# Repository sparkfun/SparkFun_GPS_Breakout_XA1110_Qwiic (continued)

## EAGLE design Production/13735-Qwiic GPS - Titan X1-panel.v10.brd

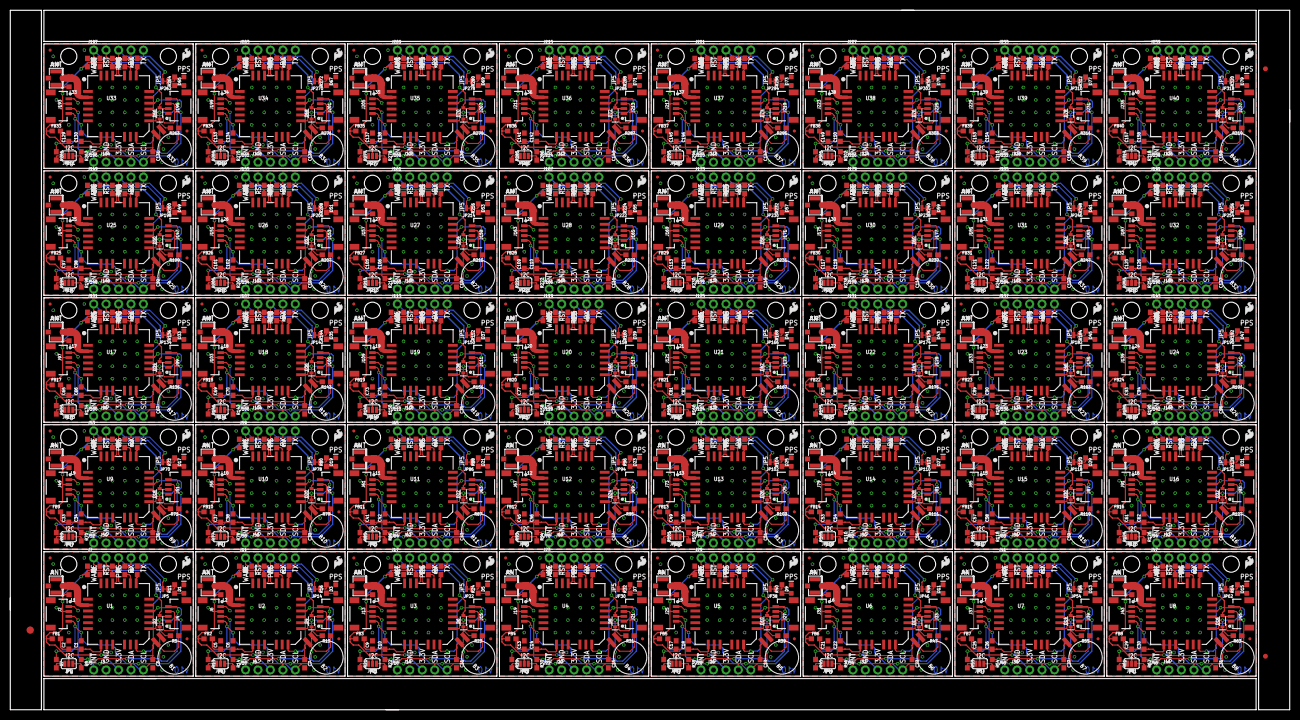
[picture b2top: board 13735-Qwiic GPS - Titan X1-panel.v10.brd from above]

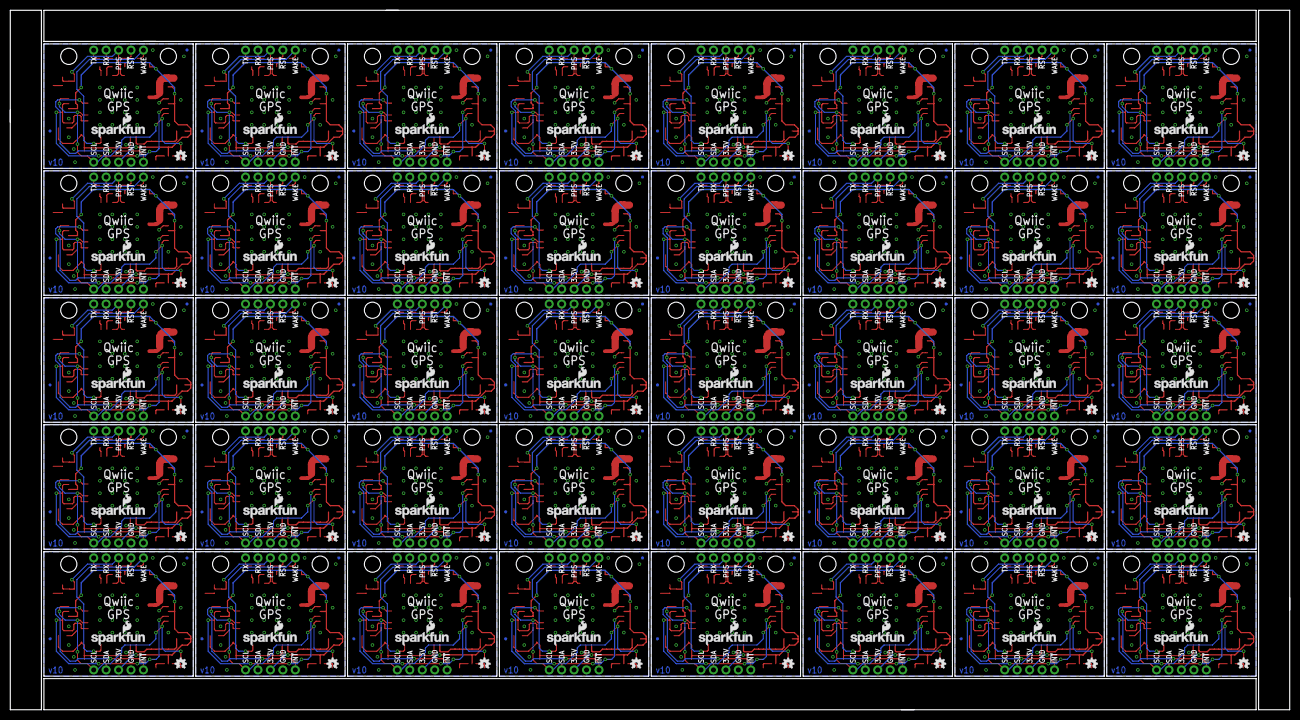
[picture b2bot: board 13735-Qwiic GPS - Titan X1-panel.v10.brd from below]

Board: 2 copper layers, 261.1 x 142.7 mm, 1403 parts (160 on the bottom side), 800 nets.

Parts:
B1, B2, B3, B4, B5, B6, B7, B8, B9, B10, B11, B12, B13, B14, B15, B16, B17, B18, B19, B20, B21, B22, B23, B24, B25, B26, B27, B28, B29, B30, B31, B32, B33, B34, B35, B36, B37, B38, B39, B40: 6.8MM_COIN_CELL; BATTCON-6.8MM
C1, C6, C10, C14, C18, C22, C26, C30, C34, C38, C42, C46, C50, C54, C58, C62, C66, C70, C74, C78, C82, C86, C90, C94, C98, C102, C106, C110, C114, C118, C122, C126, C130, C134, C138, C142, C146, C150, C154, C158: 0.1uF; 0603
C2, C3, C4, C5, C7, C8, C9, C11, C12, C13, C15, C16, C17, C19, C20, C21, C23, C24, C25, C27, C28, C29, C31, C32, C33, C35, C36, C37, C39, C40, C41, C43, C44, C45, C47, C48, C49, C51, C52, C53, C55, C56, C57, C59, C60, C61, C63, C64, C65, C67, C68, C69, C71, C72, C73, C75, C76, C77, C79, C80, C81, C83, C84, C85, C87, C88, C89, C91, C92, C93, C95, C96, C97, C99, C100, C101, C103, C104, C105, C107, C108, C109, C111, C112, C113, C115, C116, C117, C119, C120, C121, C123, C124, C125, C127, C128, C129, C131, C132, C133, C135, C136, C137, C139, C140, C141, C143, C144, C145, C147, C148, C149, C151, C152, C153, C155, C156, C157, C159, C160: 1.0uF; 0603
D1, D3, D5, D7, D9, D11, D13, D15, D17, D19, D21, D23, D25, D27, D29, D31, D33, D35, D37, D39, D41, D43, D45, D47, D49, D51, D53, D55, D57, D59, D61, D63, D65, D67, D69, D71, D73, D75, D77, D79: BLUE; LED-0603
D2, D4, D6, D8, D10, D12, D14, D16, D18, D20, D22, D24, D26, D28, D30, D32, D34, D36, D38, D40, D42, D44, D46, D48, D50, D52, D54, D56, D58, D60, D62, D64, D66, D68, D70, D72, D74, D76, D78, D80: 0.5A/40V/420mV; SOD-323
E$1: FIDUCIAL-1.5X3
E$7, E$8: FIDUCIAL-1X2
FB1, FB2, FB3, FB4, FB5, FB6, FB7, FB8, FB9, FB10, FB11, FB12, FB13, FB14, FB15, FB16, FB17, FB18, FB19, FB20, FB21, FB22, FB23, FB24, FB25, FB26, FB27, FB28, FB29, FB30, FB31, FB32, FB33, FB34, FB35, FB36, FB37, FB38, FB39, FB40: 600Ohm/100MHz; 0603
J1, J12, J18, J24, J30, J36, J42, J48, J54, J60, J66, J72, J78, J84, J90, J96, J102, J108, J114, J120, J126, J132, J138, J144, J150, J156, J162, J168, J174, J180, J186, J192, J198, J204, J210, J216, J222, J228, J234, J240: U.FL
J2, J4, J6, J9, J13, J15, J19, J21, J25, J27, J31, J33, J37, J39, J43, J45, J49, J51, J55, J57, J61, J63, J67, J69, J73, J75, J79, J81, J85, J87, J91, J93, J97, J99, J103, J105, J109, J111, J115, J117, J121, J123, J127, J129, J133, J135, J139, J141, J145, J147, J151, J153, J157, J159, J163, J165, J169, J171, J175, J177, J181, J183, J187, J189, J193, J195, J199, J201, J205, J207, J211, J213, J217, J219, J223, J225, J229, J231, J235, J237: Qwiic Right Angle; 1X04_1MM_RA
J3, J8, J14, J20, J26, J32, J38, J44, J50, J56, J62, J68, J74, J80, J86, J92, J98, J104, J110, J116, J122, J128, J134, J140, J146, J152, J158, J164, J170, J176, J182, J188, J194, J200, J206, J212, J218, J224, J230, J236: PTH; 1X04_NO_SILK
J5, J10, J16, J22, J28, J34, J40, J46, J52, J58, J64, J70, J76, J82, J88, J94, J100, J106, J112, J118, J124, J130, J136, J142, J148, J154, J160, J166, J172, J178, J184, J190, J196, J202, J208, J214, J220, J226, J232, J238: 1X01_NO_SILK
J7, J11, J17, J23, J29, J35, J41, J47, J53, J59, J65, J71, J77, J83, J89, J95, J101, J107, J113, J119, J125, J131, J137, J143, J149, J155, J161, J167, J173, J179, J185, J191, J197, J203, J209, J215, J221, J227, J233, J239: 1X05_NO_SILK
JP1, JP13, JP21, JP29, JP37, JP45, JP53, JP61, JP69, JP77, JP85, JP93, JP101, JP109, JP117, JP125, JP133, JP141, JP149, JP157, JP165, JP173, JP181, JP189, JP197, JP205, JP213, JP221, JP229, JP237, JP245, JP253, JP261, JP269, JP277, JP285, JP293, JP301, JP309, JP317: SMT-JUMPER_3_2-NC_PASTE_SILK
JP2, JP6, JP7, JP8, JP11, JP12, JP15, JP16, JP19, JP20, JP23, JP24, JP27, JP28, JP31, JP32, JP35, JP36, JP39, JP40, JP43, JP44, JP47, JP48, JP51, JP52, JP55, JP56, JP59, JP60, JP63, JP64, JP67, JP68, JP71, JP72, JP75, JP76, JP79, JP80, JP83, JP84, JP87, JP88, JP91, JP92, JP95, JP96, JP99, JP100, JP103, JP104, JP107, JP108, JP111, JP112, JP115, JP116, JP119, JP120, JP123, JP124, JP127, JP128, JP131, JP132, JP135, JP136, JP139, JP140, JP143, JP144, JP147, JP148, JP151, JP152, JP155, JP156, JP159, JP160, JP163, JP164, JP167, JP168, JP171, JP172, JP175, JP176, JP179, JP180, JP183, JP184, JP187, JP188, JP191, JP192, JP195, JP196, JP199, JP200, JP203, JP204, JP207, JP208, JP211, JP212, JP215, JP216, JP219, JP220, JP223, JP224, JP227, JP228, JP231, JP232, JP235, JP236, JP239, JP240, JP243, JP244, JP247, JP248, JP251, JP252, JP255, JP256, JP259, JP260, JP263, JP264, JP267, JP268, JP271, JP272, JP275, JP276, JP279, JP280, JP283, JP284, JP287, JP288, JP291, JP292, JP295, JP296, JP299, JP300, JP303, JP304, JP307, JP308, JP311, JP312, JP315, JP316, JP319, JP320: FIDUCIALUFIDUCIAL; MICRO-FIDUCIAL
JP3, JP4, JP9, JP10, JP17, JP18, JP25, JP26, JP33, JP34, JP41, JP42, JP49, JP50, JP57, JP58, JP65, JP66, JP73, JP74, JP81, JP82, JP89, JP90, JP97, JP98, JP105, JP106, JP113, JP114, JP121, JP122, JP129, JP130, JP137, JP138, JP145, JP146, JP153, JP154, JP161, JP162, JP169, JP170, JP177, JP178, JP185, JP186, JP193, JP194, JP201, JP202, JP209, JP210, JP217, JP218, JP225, JP226, JP233, JP234, JP241, JP242, JP249, JP250, JP257, JP258, JP265, JP266, JP273, JP274, JP281, JP282, JP289, JP290, JP297, JP298, JP305, JP306, JP313, JP314: STAND-OFF
JP5, JP14, JP22, JP30, JP38, JP46, JP54, JP62, JP70, JP78, JP86, JP94, JP102, JP110, JP118, JP126, JP134, JP142, JP150, JP158, JP166, JP174, JP182, JP190, JP198, JP206, JP214, JP222, JP230, JP238, JP246, JP254, JP262, JP270, JP278, JP286, JP294, JP302, JP310, JP318: SMT-JUMPER_2_NC_TRACE_NO-SILK
L1, L2, L3, L4, L5, L6, L7, L8, L9, L10, L11, L12, L13, L14, L15, L16, L17, L18, L19, L20, L21, L22, L23, L24, L25, L26, L27, L28, L29, L30, L31, L32, L33, L34, L35, L36, L37, L38, L39, L40: 33nH/±5%/500mA; 0603
LOGO1, LOGO3, LOGO5, LOGO7, LOGO9, LOGO11, LOGO13, LOGO15, LOGO17, LOGO19, LOGO21, LOGO23, LOGO25, LOGO27, LOGO29, LOGO31, LOGO33, LOGO35, LOGO37, LOGO39, LOGO41, LOGO43, LOGO45, LOGO47, LOGO49, LOGO51, LOGO53, LOGO55, LOGO57, LOGO59, LOGO61, LOGO63, LOGO65, LOGO67, LOGO69, LOGO71, LOGO73, LOGO75, LOGO77, LOGO79: OSHW-LOGOMINI; OSHW-LOGO-MINI
LOGO2, LOGO4, LOGO6, LOGO8, LOGO10, LOGO12, LOGO14, LOGO16, LOGO18, LOGO20, LOGO22, LOGO24, LOGO26, LOGO28, LOGO30, LOGO32, LOGO34, LOGO36, LOGO38, LOGO40, LOGO42, LOGO44, LOGO46, LOGO48, LOGO50, LOGO52, LOGO54, LOGO56, LOGO58, LOGO60, LOGO62, LOGO64, LOGO66, LOGO68, LOGO70, LOGO72, LOGO74, LOGO76, LOGO78, LOGO80: SFE_LOGO_NAME_FLAME.1_INCH; SFE_LOGO_NAME_FLAME_.1
R1, R2, R4, R9, R17, R18, R25, R26, R33, R34, R41, R42, R49, R50, R57, R58, R65, R66, R73, R74, R81, R82, R89, R90, R97, R98, R105, R106, R113, R114, R121, R122, R129, R130, R137, R138, R145, R146, R153, R154, R161, R162, R169, R170, R177, R178, R185, R186, R193, R194, R201, R202, R209, R210, R217, R218, R225, R226, R233, R234, R241, R242, R249, R250, R257, R258, R265, R266, R273, R274, R281, R282, R289, R290, R297, R298, R305, R306, R313, R314: 10k; 0603
R3, R6, R10, R11, R12, R16, R19, R20, R24, R27, R28, R32, R35, R36, R40, R43, R44, R48, R51, R52, R56, R59, R60, R64, R67, R68, R72, R75, R76, R80, R83, R84, R88, R91, R92, R96, R99, R100, R104, R107, R108, R112, R115, R116, R120, R123, R124, R128, R131, R132, R136, R139, R140, R144, R147, R148, R152, R155, R156, R160, R163, R164, R168, R171, R172, R176, R179, R180, R184, R187, R188, R192, R195, R196, R200, R203, R204, R208, R211, R212, R216, R219, R220, R224, R227, R228, R232, R235, R236, R240, R243, R244, R248, R251, R252, R256, R259, R260, R264, R267, R268, R272, R275, R276, R280, R283, R284, R288, R291, R292, R296, R299, R300, R304, R307, R308, R312, R315, R316, R320: 470; 0603
R5, R15, R23, R31, R39, R47, R55, R63, R71, R79, R87, R95, R103, R111, R119, R127, R135, R143, R151, R159, R167, R175, R183, R191, R199, R207, R215, R223, R231, R239, R247, R255, R263, R271, R279, R287, R295, R303, R311, R319: 1k; 0603
R7, R8, R13, R14, R21, R22, R29, R30, R37, R38, R45, R46, R53, R54, R61, R62, R69, R70, R77, R78, R85, R86, R93, R94, R101, R102, R109, R110, R117, R118, R125, R126, R133, R134, R141, R142, R149, R150, R157, R158, R165, R166, R173, R174, R181, R182, R189, R190, R197, R198, R205, R206, R213, R214, R221, R222, R229, R230, R237, R238, R245, R246, R253, R254, R261, R262, R269, R270, R277, R278, R285, R286, R293, R294, R301, R302, R309, R310, R317, R318: 4.7k; 0603
U1, U2, U3, U4, U5, U6, U7, U8, U9, U10, U11, U12, U13, U14, U15, U16, U17, U18, U19, U20, U21, U22, U23, U24, U25, U26, U27, U28, U29, U30, U31, U32, U33, U34, U35, U36, U37, U38, U39, U40: Titan X1 GPS; TITAN_X1_GPS
U$1, U$2, U$3, U$4, U$5, U$6, U$7, U$8, U$9, U$10, U$11, U$12, U$13, U$14, U$15, U$16, U$17, U$18, U$19, U$20, U$21, U$22, U$23, U$24, U$25, U$26, U$27, U$28, U$29, U$30, U$31, U$32, U$33, U$34, U$35, U$36, U$37, U$38, U$39, U$40: SFE_LOGO_FLAME_.1

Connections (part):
3.3V: C4.2, D2.A, FB1.1, J2.2, J3.2, J4.2, JP1.2, L1.2, R2.2
3.3V1: C8.2, D4.A, FB2.1, J6.2, J8.2, J9.2, JP13.2, L2.2, R9.2
3.3V2: C12.2, D6.A, FB3.1, J13.2, J14.2, J15.2, JP21.2, L3.2, R18.2
3.3V3: C16.2, D8.A, FB4.1, J19.2, J20.2, J21.2, JP29.2, L4.2, R26.2
3.3V4: C20.2, D10.A, FB5.1, J25.2, J26.2, J27.2, JP37.2, L5.2, R34.2
3.3V5: C24.2, D12.A, FB6.1, J31.2, J32.2, J33.2, JP45.2, L6.2, R42.2
3.3V6: C28.2, D14.A, FB7.1, J37.2, J38.2, J39.2, JP53.2, L7.2, R50.2
3.3V7: C32.2, D16.A, FB8.1, J43.2, J44.2, J45.2, JP61.2, L8.2, R58.2
3.3V8: C36.2, D18.A, FB9.1, J49.2, J50.2, J51.2, JP69.2, L9.2, R66.2
3.3V9: C40.2, D20.A, FB10.1, J55.2, J56.2, J57.2, JP77.2, L10.2, R74.2
3.3V10: C44.2, D22.A, FB11.1, J61.2, J62.2, J63.2, JP85.2, L11.2, R82.2
3.3V11: C48.2, D24.A, FB12.1, J67.2, J68.2, J69.2, JP93.2, L12.2, R90.2
3.3V12: C52.2, D26.A, FB13.1, J73.2, J74.2, J75.2, JP101.2, L13.2, R98.2
3.3V13: C56.2, D28.A, FB14.1, J79.2, J80.2, J81.2, JP109.2, L14.2, R106.2
3.3V14: C60.2, D30.A, FB15.1, J85.2, J86.2, J87.2, JP117.2, L15.2, R114.2
3.3V15: C64.2, D32.A, FB16.1, J91.2, J92.2, J93.2, JP125.2, L16.2, R122.2
3.3V16: C68.2, D34.A, FB17.1, J97.2, J98.2, J99.2, JP133.2, L17.2, R130.2
3.3V17: C72.2, D36.A, FB18.1, J103.2, J104.2, J105.2, JP141.2, L18.2, R138.2
3.3V18: C76.2, D38.A, FB19.1, J109.2, J110.2, J111.2, JP149.2, L19.2, R146.2
3.3V19: C80.2, D40.A, FB20.1, J115.2, J116.2, J117.2, JP157.2, L20.2, R154.2
3.3V20: C84.2, D42.A, FB21.1, J121.2, J122.2, J123.2, JP165.2, L21.2, R162.2
3.3V21: C88.2, D44.A, FB22.1, J127.2, J128.2, J129.2, JP173.2, L22.2, R170.2
3.3V22: C92.2, D46.A, FB23.1, J133.2, J134.2, J135.2, JP181.2, L23.2, R178.2
3.3V23: C96.2, D48.A, FB24.1, J139.2, J140.2, J141.2, JP189.2, L24.2, R186.2
3.3V24: C100.2, D50.A, FB25.1, J145.2, J146.2, J147.2, JP197.2, L25.2, R194.2
3.3V25: C104.2, D52.A, FB26.1, J151.2, J152.2, J153.2, JP205.2, L26.2, R202.2
3.3V26: C108.2, D54.A, FB27.1, J157.2, J158.2, J159.2, JP213.2, L27.2, R210.2
3.3V27: C112.2, D56.A, FB28.1, J163.2, J164.2, J165.2, JP221.2, L28.2, R218.2
3.3V28: C116.2, D58.A, FB29.1, J169.2, J170.2, J171.2, JP229.2, L29.2, R226.2
3.3V29: C120.2, D60.A, FB30.1, J175.2, J176.2, J177.2, JP237.2, L30.2, R234.2
3.3V30: C124.2, D62.A, FB31.1, J181.2, J182.2, J183.2, JP245.2, L31.2, R242.2
3.3V31: C128.2, D64.A, FB32.1, J187.2, J188.2, J189.2, JP253.2, L32.2, R250.2
3.3V32: C132.2, D66.A, FB33.1, J193.2, J194.2, J195.2, JP261.2, L33.2, R258.2
3.3V33: C136.2, D68.A, FB34.1, J199.2, J200.2, J201.2, JP269.2, L34.2, R266.2
3.3V34: C140.2, D70.A, FB35.1, J205.2, J206.2, J207.2, JP277.2, L35.2, R274.2
3.3V35: C144.2, D72.A, FB36.1, J211.2, J212.2, J213.2, JP285.2, L36.2, R282.2
3.3V36: C148.2, D74.A, FB37.1, J217.2, J218.2, J219.2, JP293.2, L37.2, R290.2
3.3V37: C152.2, D76.A, FB38.1, J223.2, J224.2, J225.2, JP301.2, L38.2, R298.2
3.3V38: C156.2, D78.A, FB39.1, J229.2, J230.2, J231.2, JP309.2, L39.2, R306.2
3.3V39: C160.2, D80.A, FB40.1, J235.2, J236.2, J237.2, JP317.2, L40.2, R314.2
!RESET: J7.2, R2.1, U1.22
!RESET1: J11.2, R9.1, U2.22
!RESET2: J17.2, R18.1, U3.22
!RESET3: J23.2, R26.1, U4.22
!RESET4: J29.2, R34.1, U5.22
!RESET5: J35.2, R42.1, U6.22
!RESET6: J41.2, R50.1, U7.22
!RESET7: J47.2, R58.1, U8.22
!RESET8: J53.2, R66.1, U9.22
!RESET9: J59.2, R74.1, U10.22
!RESET10: J65.2, R82.1, U11.22
!RESET11: J71.2, R90.1, U12.22
!RESET12: J77.2, R98.1, U13.22
!RESET13: J83.2, R106.1, U14.22
!RESET14: J89.2, R114.1, U15.22
!RESET15: J95.2, R122.1, U16.22
!RESET16: J101.2, R130.1, U17.22
!RESET17: J107.2, R138.1, U18.22
!RESET18: J113.2, R146.1, U19.22
!RESET19: J119.2, R154.1, U20.22
!RESET20: J125.2, R162.1, U21.22
!RESET21: J131.2, R170.1, U22.22
!RESET22: J137.2, R178.1, U23.22
!RESET23: J143.2, R186.1, U24.22
!RESET24: J149.2, R194.1, U25.22
!RESET25: J155.2, R202.1, U26.22
!RESET26: J161.2, R210.1, U27.22
!RESET27: J167.2, R218.1, U28.22
!RESET28: J173.2, R226.1, U29.22
!RESET29: J179.2, R234.1, U30.22
!RESET30: J185.2, R242.1, U31.22
!RESET31: J191.2, R250.1, U32.22
!RESET32: J197.2, R258.1, U33.22
!RESET33: J203.2, R266.1, U34.22
!RESET34: J209.2, R274.1, U35.22
!RESET35: J215.2, R282.1, U36.22
!RESET36: J221.2, R290.1, U37.22
!RESET37: J227.2, R298.1, U38.22
!RESET38: J233.2, R306.1, U39.22
!RESET39: J239.2, R314.1, U40.22
BACKUP: B1.+, C3.1, R5.1, U1.8
BACKUP1: B2.+, C7.1, R15.1, U2.8
BACKUP2: B3.+, C11.1, R23.1, U3.8
BACKUP3: B4.+, C15.1, R31.1, U4.8
BACKUP4: B5.+, C19.1, R39.1, U5.8
BACKUP5: B6.+, C23.1, R47.1, U6.8
BACKUP6: B7.+, C27.1, R55.1, U7.8
BACKUP7: B8.+, C31.1, R63.1, U8.8
BACKUP8: B9.+, C35.1, R71.1, U9.8
BACKUP9: B10.+, C39.1, R79.1, U10.8
BACKUP10: B11.+, C43.1, R87.1, U11.8
BACKUP11: B12.+, C47.1, R95.1, U12.8
BACKUP12: B13.+, C51.1, R103.1, U13.8
BACKUP13: B14.+, C55.1, R111.1, U14.8
BACKUP14: B15.+, C59.1, R119.1, U15.8
BACKUP15: B16.+, C63.1, R127.1, U16.8
BACKUP16: B17.+, C67.1, R135.1, U17.8
BACKUP17: B18.+, C71.1, R143.1, U18.8
BACKUP18: B19.+, C75.1, R151.1, U19.8
BACKUP19: B20.+, C79.1, R159.1, U20.8
BACKUP20: B21.+, C83.1, R167.1, U21.8
BACKUP21: B22.+, C87.1, R175.1, U22.8
BACKUP22: B23.+, C91.1, R183.1, U23.8
BACKUP23: B24.+, C95.1, R191.1, U24.8
BACKUP24: B25.+, C99.1, R199.1, U25.8
BACKUP25: B26.+, C103.1, R207.1, U26.8
BACKUP26: B27.+, C107.1, R215.1, U27.8
BACKUP27: B28.+, C111.1, R223.1, U28.8
BACKUP28: B29.+, C115.1, R231.1, U29.8
BACKUP29: B30.+, C119.1, R239.1, U30.8
BACKUP30: B31.+, C123.1, R247.1, U31.8
BACKUP31: B32.+, C127.1, R255.1, U32.8
BACKUP32: B33.+, C131.1, R263.1, U33.8
BACKUP33: B34.+, C135.1, R271.1, U34.8
BACKUP34: B35.+, C139.1, R279.1, U35.8
BACKUP35: B36.+, C143.1, R287.1, U36.8
BACKUP36: B37.+, C147.1, R295.1, U37.8
BACKUP37: B38.+, C151.1, R303.1, U38.8
BACKUP38: B39.+, C155.1, R311.1, U39.8
BACKUP39: B40.+, C159.1, R319.1, U40.8
EXT_ANT: J1.FEED, L1.1, U1.2
EXT_ANT1: J12.FEED, L2.1, U2.2
EXT_ANT2: J18.FEED, L3.1, U3.2
EXT_ANT3: J24.FEED, L4.1, U4.2
EXT_ANT4: J30.FEED, L5.1, U5.2
EXT_ANT5: J36.FEED, L6.1, U6.2
EXT_ANT6: J42.FEED, L7.1, U7.2
EXT_ANT7: J48.FEED, L8.1, U8.2
EXT_ANT8: J54.FEED, L9.1, U9.2
EXT_ANT9: J60.FEED, L10.1, U10.2
EXT_ANT10: J66.FEED, L11.1, U11.2
EXT_ANT11: J72.FEED, L12.1, U12.2
EXT_ANT12: J78.FEED, L13.1, U13.2
EXT_ANT13: J84.FEED, L14.1, U14.2
EXT_ANT14: J90.FEED, L15.1, U15.2
EXT_ANT15: J96.FEED, L16.1, U16.2
EXT_ANT16: J102.FEED, L17.1, U17.2
EXT_ANT17: J108.FEED, L18.1, U18.2
EXT_ANT18: J114.FEED, L19.1, U19.2
EXT_ANT19: J120.FEED, L20.1, U20.2
EXT_ANT20: J126.FEED, L21.1, U21.2
EXT_ANT21: J132.FEED, L22.1, U22.2
EXT_ANT22: J138.FEED, L23.1, U23.2
EXT_ANT23: J144.FEED, L24.1, U24.2
EXT_ANT24: J150.FEED, L25.1, U25.2
EXT_ANT25: J156.FEED, L26.1, U26.2
EXT_ANT26: J162.FEED, L27.1, U27.2
EXT_ANT27: J168.FEED, L28.1, U28.2
EXT_ANT28: J174.FEED, L29.1, U29.2
EXT_ANT29: J180.FEED, L30.1, U30.2
EXT_ANT30: J186.FEED, L31.1, U31.2
EXT_ANT31: J192.FEED, L32.1, U32.2
EXT_ANT32: J198.FEED, L33.1, U33.2
EXT_ANT33: J204.FEED, L34.1, U34.2
EXT_ANT34: J210.FEED, L35.1, U35.2
EXT_ANT35: J216.FEED, L36.1, U36.2
EXT_ANT36: J222.FEED, L37.1, U37.2
EXT_ANT37: J228.FEED, L38.1, U38.2
EXT_ANT38: J234.FEED, L39.1, U39.2
EXT_ANT39: J240.FEED, L40.1, U40.2
GND: B1.-, C1.2, C2.2, C3.2, C4.1, D1.C, J1.1, J1.2, J2.1, J3.1, J4.1, R1.1, U1.1, U1.3, U1.4, U1.5, U1.6, U1.9, U1.10, U1.11, U1.24
GND1: B2.-, C5.2, C6.2, C7.2, C8.1, D3.C, J6.1, J8.1, J9.1, J12.1, J12.2, R4.1, U2.1, U2.3, U2.4, U2.5, U2.6, U2.9, U2.10, U2.11, U2.24
GND2: B3.-, C9.2, C10.2, C11.2, C12.1, D5.C, J13.1, J14.1, J15.1, J18.1, J18.2, R17.1, U3.1, U3.3, U3.4, U3.5, U3.6, U3.9, U3.10, U3.11, U3.24
GND3: B4.-, C13.2, C14.2, C15.2, C16.1, D7.C, J19.1, J20.1, J21.1, J24.1, J24.2, R25.1, U4.1, U4.3, U4.4, U4.5, U4.6, U4.9, U4.10, U4.11, U4.24
GND4: B5.-, C17.2, C18.2, C19.2, C20.1, D9.C, J25.1, J26.1, J27.1, J30.1, J30.2, R33.1, U5.1, U5.3, U5.4, U5.5, U5.6, U5.9, U5.10, U5.11, U5.24
GND5: B6.-, C21.2, C22.2, C23.2, C24.1, D11.C, J31.1, J32.1, J33.1, J36.1, J36.2, R41.1, U6.1, U6.3, U6.4, U6.5, U6.6, U6.9, U6.10, U6.11, U6.24
GND6: B7.-, C25.2, C26.2, C27.2, C28.1, D13.C, J37.1, J38.1, J39.1, J42.1, J42.2, R49.1, U7.1, U7.3, U7.4, U7.5, U7.6, U7.9, U7.10, U7.11, U7.24
GND7: B8.-, C29.2, C30.2, C31.2, C32.1, D15.C, J43.1, J44.1, J45.1, J48.1, J48.2, R57.1, U8.1, U8.3, U8.4, U8.5, U8.6, U8.9, U8.10, U8.11, U8.24
GND8: B9.-, C33.2, C34.2, C35.2, C36.1, D17.C, J49.1, J50.1, J51.1, J54.1, J54.2, R65.1, U9.1, U9.3, U9.4, U9.5, U9.6, U9.9, U9.10, U9.11, U9.24
GND9: B10.-, C37.2, C38.2, C39.2, C40.1, D19.C, J55.1, J56.1, J57.1, J60.1, J60.2, R73.1, U10.1, U10.3, U10.4, U10.5, U10.6, U10.9, U10.10, U10.11, U10.24
GND10: B11.-, C41.2, C42.2, C43.2, C44.1, D21.C, J61.1, J62.1, J63.1, J66.1, J66.2, R81.1, U11.1, U11.3, U11.4, U11.5, U11.6, U11.9, U11.10, U11.11, U11.24
GND11: B12.-, C45.2, C46.2, C47.2, C48.1, D23.C, J67.1, J68.1, J69.1, J72.1, J72.2, R89.1, U12.1, U12.3, U12.4, U12.5, U12.6, U12.9, U12.10, U12.11, U12.24
GND12: B13.-, C49.2, C50.2, C51.2, C52.1, D25.C, J73.1, J74.1, J75.1, J78.1, J78.2, R97.1, U13.1, U13.3, U13.4, U13.5, U13.6, U13.9, U13.10, U13.11, U13.24
GND13: B14.-, C53.2, C54.2, C55.2, C56.1, D27.C, J79.1, J80.1, J81.1, J84.1, J84.2, R105.1, U14.1, U14.3, U14.4, U14.5, U14.6, U14.9, U14.10, U14.11, U14.24
GND14: B15.-, C57.2, C58.2, C59.2, C60.1, D29.C, J85.1, J86.1, J87.1, J90.1, J90.2, R113.1, U15.1, U15.3, U15.4, U15.5, U15.6, U15.9, U15.10, U15.11, U15.24
GND15: B16.-, C61.2, C62.2, C63.2, C64.1, D31.C, J91.1, J92.1, J93.1, J96.1, J96.2, R121.1, U16.1, U16.3, U16.4, U16.5, U16.6, U16.9, U16.10, U16.11, U16.24
GND16: B17.-, C65.2, C66.2, C67.2, C68.1, D33.C, J97.1, J98.1, J99.1, J102.1, J102.2, R129.1, U17.1, U17.3, U17.4, U17.5, U17.6, U17.9, U17.10, U17.11, U17.24
GND17: B18.-, C69.2, C70.2, C71.2, C72.1, D35.C, J103.1, J104.1, J105.1, J108.1, J108.2, R137.1, U18.1, U18.3, U18.4, U18.5, U18.6, U18.9, U18.10, U18.11, U18.24
GND18: B19.-, C73.2, C74.2, C75.2, C76.1, D37.C, J109.1, J110.1, J111.1, J114.1, J114.2, R145.1, U19.1, U19.3, U19.4, U19.5, U19.6, U19.9, U19.10, U19.11, U19.24
GND19: B20.-, C77.2, C78.2, C79.2, C80.1, D39.C, J115.1, J116.1, J117.1, J120.1, J120.2, R153.1, U20.1, U20.3, U20.4, U20.5, U20.6, U20.9, U20.10, U20.11, U20.24
GND20: B21.-, C81.2, C82.2, C83.2, C84.1, D41.C, J121.1, J122.1, J123.1, J126.1, J126.2, R161.1, U21.1, U21.3, U21.4, U21.5, U21.6, U21.9, U21.10, U21.11, U21.24
GND21: B22.-, C85.2, C86.2, C87.2, C88.1, D43.C, J127.1, J128.1, J129.1, J132.1, J132.2, R169.1, U22.1, U22.3, U22.4, U22.5, U22.6, U22.9, U22.10, U22.11, U22.24
GND22: B23.-, C89.2, C90.2, C91.2, C92.1, D45.C, J133.1, J134.1, J135.1, J138.1, J138.2, R177.1, U23.1, U23.3, U23.4, U23.5, U23.6, U23.9, U23.10, U23.11, U23.24
GND23: B24.-, C93.2, C94.2, C95.2, C96.1, D47.C, J139.1, J140.1, J141.1, J144.1, J144.2, R185.1, U24.1, U24.3, U24.4, U24.5, U24.6, U24.9, U24.10, U24.11, U24.24
GND24: B25.-, C97.2, C98.2, C99.2, C100.1, D49.C, J145.1, J146.1, J147.1, J150.1, J150.2, R193.1, U25.1, U25.3, U25.4, U25.5, U25.6, U25.9, U25.10, U25.11, U25.24
GND25: B26.-, C101.2, C102.2, C103.2, C104.1, D51.C, J151.1, J152.1, J153.1, J156.1, J156.2, R201.1, U26.1, U26.3, U26.4, U26.5, U26.6, U26.9, U26.10, U26.11, U26.24
GND26: B27.-, C105.2, C106.2, C107.2, C108.1, D53.C, J157.1, J158.1, J159.1, J162.1, J162.2, R209.1, U27.1, U27.3, U27.4, U27.5, U27.6, U27.9, U27.10, U27.11, U27.24
GND27: B28.-, C109.2, C110.2, C111.2, C112.1, D55.C, J163.1, J164.1, J165.1, J168.1, J168.2, R217.1, U28.1, U28.3, U28.4, U28.5, U28.6, U28.9, U28.10, U28.11, U28.24
GND28: B29.-, C113.2, C114.2, C115.2, C116.1, D57.C, J169.1, J170.1, J171.1, J174.1, J174.2, R225.1, U29.1, U29.3, U29.4, U29.5, U29.6, U29.9, U29.10, U29.11, U29.24
GND29: B30.-, C117.2, C118.2, C119.2, C120.1, D59.C, J175.1, J176.1, J177.1, J180.1, J180.2, R233.1, U30.1, U30.3, U30.4, U30.5, U30.6, U30.9, U30.10, U30.11, U30.24
GND30: B31.-, C121.2, C122.2, C123.2, C124.1, D61.C, J181.1, J182.1, J183.1, J186.1, J186.2, R241.1, U31.1, U31.3, U31.4, U31.5, U31.6, U31.9, U31.10, U31.11, U31.24
GND31: B32.-, C125.2, C126.2, C127.2, C128.1, D63.C, J187.1, J188.1, J189.1, J192.1, J192.2, R249.1, U32.1, U32.3, U32.4, U32.5, U32.6, U32.9, U32.10, U32.11, U32.24
GND32: B33.-, C129.2, C130.2, C131.2, C132.1, D65.C, J193.1, J194.1, J195.1, J198.1, J198.2, R257.1, U33.1, U33.3, U33.4, U33.5, U33.6, U33.9, U33.10, U33.11, U33.24
GND33: B34.-, C133.2, C134.2, C135.2, C136.1, D67.C, J199.1, J200.1, J201.1, J204.1, J204.2, R265.1, U34.1, U34.3, U34.4, U34.5, U34.6, U34.9, U34.10, U34.11, U34.24
GND34: B35.-, C137.2, C138.2, C139.2, C140.1, D69.C, J205.1, J206.1, J207.1, J210.1, J210.2, R273.1, U35.1, U35.3, U35.4, U35.5, U35.6, U35.9, U35.10, U35.11, U35.24
GND35: B36.-, C141.2, C142.2, C143.2, C144.1, D71.C, J211.1, J212.1, J213.1, J216.1, J216.2, R281.1, U36.1, U36.3, U36.4, U36.5, U36.6, U36.9, U36.10, U36.11, U36.24
GND36: B37.-, C145.2, C146.2, C147.2, C148.1, D73.C, J217.1, J218.1, J219.1, J222.1, J222.2, R289.1, U37.1, U37.3, U37.4, U37.5, U37.6, U37.9, U37.10, U37.11, U37.24
GND37: B38.-, C149.2, C150.2, C151.2, C152.1, D75.C, J223.1, J224.1, J225.1, J228.1, J228.2, R297.1, U38.1, U38.3, U38.4, U38.5, U38.6, U38.9, U38.10, U38.11, U38.24
GND38: B39.-, C153.2, C154.2, C155.2, C156.1, D77.C, J229.1, J230.1, J231.1, J234.1, J234.2, R305.1, U39.1, U39.3, U39.4, U39.5, U39.6, U39.9, U39.10, U39.11, U39.24
GND39: B40.-, C157.2, C158.2, C159.2, C160.1, D79.C, J235.1, J236.1, J237.1, J240.1, J240.2, R313.1, U40.1, U40.3, U40.4, U40.5, U40.6, U40.9, U40.10, U40.11, U40.24
INT: J5.1, U1.16
INT1: J10.1, U2.16
INT2: J16.1, U3.16
INT3: J22.1, U4.16
INT4: J28.1, U5.16
INT5: J34.1, U6.16
INT6: J40.1, U7.16
INT7: J46.1, U8.16
INT8: J52.1, U9.16
INT9: J58.1, U10.16
INT10: J64.1, U11.16
INT11: J70.1, U12.16
INT12: J76.1, U13.16
INT13: J82.1, U14.16
INT14: J88.1, U15.16
INT15: J94.1, U16.16
INT16: J100.1, U17.16
INT17: J106.1, U18.16
INT18: J112.1, U19.16
INT19: J118.1, U20.16
INT20: J124.1, U21.16
INT21: J130.1, U22.16
INT22: J136.1, U23.16
INT23: J142.1, U24.16
INT24: J148.1, U25.16
INT25: J154.1, U26.16
INT26: J160.1, U27.16
INT27: J166.1, U28.16
INT28: J172.1, U29.16
INT29: J178.1, U30.16
INT30: J184.1, U31.16
INT31: J190.1, U32.16
INT32: J196.1, U33.16
INT33: J202.1, U34.16
INT34: J208.1, U35.16
INT35: J214.1, U36.16
INT36: J220.1, U37.16
INT37: J226.1, U38.16
INT38: J232.1, U39.16
INT39: J238.1, U40.16
unnamed: JP13.1, R14.2
unnamed: D1.A, R11.1
unnamed: JP13.3, R13.2
unnamed: JP5.1, R11.2
unnamed: JP1.1, R8.2
unnamed: D2.C, R5.2
unnamed: D3.A, R16.1
unnamed: JP1.3, R7.2
unnamed: JP14.1, R16.2
unnamed: D4.C, R15.2
unnamed: JP21.1, R22.2
unnamed: JP21.3, R21.2
unnamed: D5.A, R24.1
unnamed: JP22.1, R24.2
unnamed: D6.C, R23.2
unnamed: JP29.1, R30.2
unnamed: JP29.3, R29.2
unnamed: D7.A, R32.1
unnamed: JP30.1, R32.2
unnamed: D8.C, R31.2
unnamed: JP37.1, R38.2
unnamed: JP37.3, R37.2
unnamed: D9.A, R40.1
unnamed: JP38.1, R40.2
unnamed: D10.C, R39.2
unnamed: JP45.1, R46.2
unnamed: JP45.3, R45.2
unnamed: D11.A, R48.1
unnamed: JP46.1, R48.2
unnamed: D12.C, R47.2
unnamed: JP53.1, R54.2
unnamed: JP53.3, R53.2
unnamed: D13.A, R56.1
unnamed: JP54.1, R56.2
unnamed: D14.C, R55.2
unnamed: JP61.1, R62.2
unnamed: JP61.3, R61.2
unnamed: D15.A, R64.1
unnamed: JP62.1, R64.2
unnamed: D16.C, R63.2
unnamed: JP69.1, R70.2
unnamed: JP69.3, R69.2
unnamed: D17.A, R72.1
unnamed: JP70.1, R72.2
unnamed: D18.C, R71.2
unnamed: JP77.1, R78.2
unnamed: JP77.3, R77.2
unnamed: D19.A, R80.1
unnamed: JP78.1, R80.2
unnamed: D20.C, R79.2
unnamed: JP85.1, R86.2
unnamed: JP85.3, R85.2
unnamed: D21.A, R88.1
unnamed: JP86.1, R88.2
unnamed: D22.C, R87.2
unnamed: JP93.1, R94.2
unnamed: JP93.3, R93.2
unnamed: D23.A, R96.1
unnamed: JP94.1, R96.2
unnamed: D24.C, R95.2
unnamed: JP101.1, R102.2
unnamed: JP101.3, R101.2
unnamed: D25.A, R104.1
unnamed: JP102.1, R104.2
unnamed: D26.C, R103.2
unnamed: JP109.1, R110.2
unnamed: JP109.3, R109.2
unnamed: D27.A, R112.1
unnamed: JP110.1, R112.2
unnamed: D28.C, R111.2
unnamed: JP117.1, R118.2
unnamed: JP117.3, R117.2
unnamed: D29.A, R120.1
unnamed: JP118.1, R120.2
unnamed: D30.C, R119.2
unnamed: JP125.1, R126.2
unnamed: JP125.3, R125.2
unnamed: D31.A, R128.1
unnamed: JP126.1, R128.2
unnamed: D32.C, R127.2
unnamed: JP133.1, R134.2
unnamed: JP133.3, R133.2
unnamed: D33.A, R136.1
unnamed: JP134.1, R136.2
unnamed: D34.C, R135.2
unnamed: JP141.1, R142.2
unnamed: JP141.3, R141.2
unnamed: D35.A, R144.1
unnamed: JP142.1, R144.2
unnamed: D36.C, R143.2
unnamed: JP149.1, R150.2
unnamed: JP149.3, R149.2
unnamed: D37.A, R152.1
unnamed: JP150.1, R152.2
unnamed: D38.C, R151.2
unnamed: JP157.1, R158.2
unnamed: JP157.3, R157.2
unnamed: D39.A, R160.1
unnamed: JP158.1, R160.2
unnamed: D40.C, R159.2
unnamed: JP165.1, R166.2
unnamed: JP165.3, R165.2
unnamed: D41.A, R168.1
unnamed: JP166.1, R168.2
unnamed: D42.C, R167.2
unnamed: JP173.1, R174.2
unnamed: JP173.3, R173.2
unnamed: D43.A, R176.1
unnamed: JP174.1, R176.2
unnamed: D44.C, R175.2
unnamed: JP181.1, R182.2
unnamed: JP181.3, R181.2
unnamed: D45.A, R184.1
unnamed: JP182.1, R184.2
unnamed: D46.C, R183.2
unnamed: JP189.1, R190.2
unnamed: JP189.3, R189.2
unnamed: D47.A, R192.1
unnamed: JP190.1, R192.2
unnamed: D48.C, R191.2
unnamed: JP197.1, R198.2
unnamed: JP197.3, R197.2
unnamed: D49.A, R200.1
unnamed: JP198.1, R200.2
unnamed: D50.C, R199.2
unnamed: JP205.1, R206.2
unnamed: JP205.3, R205.2
unnamed: D51.A, R208.1
unnamed: JP206.1, R208.2
unnamed: D52.C, R207.2
unnamed: JP213.1, R214.2
unnamed: JP213.3, R213.2
unnamed: D53.A, R216.1
unnamed: JP214.1, R216.2
unnamed: D54.C, R215.2
unnamed: JP221.1, R222.2
unnamed: JP221.3, R221.2
unnamed: D55.A, R224.1
unnamed: JP222.1, R224.2
unnamed: D56.C, R223.2
unnamed: JP229.1, R230.2
unnamed: JP229.3, R229.2
unnamed: D57.A, R232.1
unnamed: JP230.1, R232.2
unnamed: D58.C, R231.2
unnamed: JP237.1, R238.2
unnamed: JP237.3, R237.2
unnamed: D59.A, R240.1
unnamed: JP238.1, R240.2
unnamed: D60.C, R239.2
unnamed: JP245.1, R246.2
unnamed: JP245.3, R245.2
unnamed: D61.A, R248.1
unnamed: JP246.1, R248.2
unnamed: D62.C, R247.2
unnamed: JP253.1, R254.2
unnamed: JP253.3, R253.2
unnamed: D63.A, R256.1
unnamed: JP254.1, R256.2
unnamed: D64.C, R255.2
unnamed: JP261.1, R262.2
unnamed: JP261.3, R261.2
unnamed: D65.A, R264.1
unnamed: JP262.1, R264.2
unnamed: D66.C, R263.2
unnamed: JP269.1, R270.2
unnamed: JP269.3, R269.2
unnamed: D67.A, R272.1
unnamed: JP270.1, R272.2
unnamed: D68.C, R271.2
unnamed: JP277.1, R278.2
unnamed: JP277.3, R277.2
unnamed: D69.A, R280.1
unnamed: JP278.1, R280.2
unnamed: D70.C, R279.2
unnamed: JP285.1, R286.2
unnamed: JP285.3, R285.2
unnamed: D71.A, R288.1
unnamed: JP286.1, R288.2
unnamed: D72.C, R287.2
unnamed: JP293.1, R294.2
unnamed: JP293.3, R293.2
unnamed: D73.A, R296.1
unnamed: JP294.1, R296.2
unnamed: D74.C, R295.2
unnamed: JP301.1, R302.2
unnamed: JP301.3, R301.2
unnamed: D75.A, R304.1
unnamed: JP302.1, R304.2
unnamed: D76.C, R303.2
unnamed: JP309.1, R310.2
unnamed: JP309.3, R309.2
unnamed: D77.A, R312.1
unnamed: JP310.1, R312.2
unnamed: D78.C, R311.2
unnamed: JP317.1, R318.2
unnamed: JP317.3, R317.2
unnamed: D79.A, R320.1
unnamed: JP318.1, R320.2
unnamed: D80.C, R319.2
PPS: J7.3, JP5.2, U1.21
PPS1: J11.3, JP14.2, U2.21
PPS2: J17.3, JP22.2, U3.21
PPS3: J23.3, JP30.2, U4.21
PPS4: J29.3, JP38.2, U5.21
PPS5: J35.3, JP46.2, U6.21
PPS6: J41.3, JP54.2, U7.21
PPS7: J47.3, JP62.2, U8.21
PPS8: J53.3, JP70.2, U9.21
PPS9: J59.3, JP78.2, U10.21
PPS10: J65.3, JP86.2, U11.21
PPS11: J71.3, JP94.2, U12.21
PPS12: J77.3, JP102.2, U13.21
PPS13: J83.3, JP110.2, U14.21
PPS14: J89.3, JP118.2, U15.21
PPS15: J95.3, JP126.2, U16.21
PPS16: J101.3, JP134.2, U17.21
PPS17: J107.3, JP142.2, U18.21
PPS18: J113.3, JP150.2, U19.21
PPS19: J119.3, JP158.2, U20.21
PPS20: J125.3, JP166.2, U21.21
PPS21: J131.3, JP174.2, U22.21
PPS22: J137.3, JP182.2, U23.21
PPS23: J143.3, JP190.2, U24.21
PPS24: J149.3, JP198.2, U25.21
PPS25: J155.3, JP206.2, U26.21
PPS26: J161.3, JP214.2, U27.21
PPS27: J167.3, JP222.2, U28.21
PPS28: J173.3, JP230.2, U29.21
PPS29: J179.3, JP238.2, U30.21
PPS30: J185.3, JP246.2, U31.21
PPS31: J191.3, JP254.2, U32.21
PPS32: J197.3, JP262.2, U33.21
PPS33: J203.3, JP270.2, U34.21
PPS34: J209.3, JP278.2, U35.21
PPS35: J215.3, JP286.2, U36.21
PPS36: J221.3, JP294.2, U37.21
PPS37: J227.3, JP302.2, U38.21
PPS38: J233.3, JP310.2, U39.21
PPS39: J239.3, JP318.2, U40.21
RX: J7.4, R3.2
RX1: J11.4, R10.2
RX2: J17.4, R19.2
RX3: J23.4, R27.2
RX4: J29.4, R35.2
RX5: J35.4, R43.2
RX6: J41.4, R51.2
RX7: J47.4, R59.2
RX8: J53.4, R67.2
RX9: J59.4, R75.2
RX10: J65.4, R83.2
RX11: J71.4, R91.2
RX12: J77.4, R99.2
RX13: J83.4, R107.2
RX14: J89.4, R115.2
RX15: J95.4, R123.2
RX16: J101.4, R131.2
RX17: J107.4, R139.2
RX18: J113.4, R147.2
RX19: J119.4, R155.2
RX20: J125.4, R163.2
RX21: J131.4, R171.2
RX22: J137.4, R179.2
RX23: J143.4, R187.2
RX24: J149.4, R195.2
RX25: J155.4, R203.2
RX26: J161.4, R211.2
RX27: J167.4, R219.2
RX28: J173.4, R227.2
RX29: J179.4, R235.2
RX30: J185.4, R243.2
RX31: J191.4, R251.2
RX32: J197.4, R259.2
RX33: J203.4, R267.2
RX34: J209.4, R275.2
RX35: J215.4, R283.2
RX36: J221.4, R291.2
RX37: J227.4, R299.2
RX38: J233.4, R307.2
RX39: J239.4, R315.2
RXLV: R3.1, U1.20
RXLV1: R10.1, U2.20
RXLV2: R19.1, U3.20
RXLV3: R27.1, U4.20
RXLV4: R35.1, U5.20
RXLV5: R43.1, U6.20
RXLV6: R51.1, U7.20
RXLV7: R59.1, U8.20
RXLV8: R67.1, U9.20
RXLV9: R75.1, U10.20
RXLV10: R83.1, U11.20
RXLV11: R91.1, U12.20
RXLV12: R99.1, U13.20
RXLV13: R107.1, U14.20
RXLV14: R115.1, U15.20
RXLV15: R123.1, U16.20
RXLV16: R131.1, U17.20
RXLV17: R139.1, U18.20
RXLV18: R147.1, U19.20
RXLV19: R155.1, U20.20
RXLV20: R163.1, U21.20
RXLV21: R171.1, U22.20
RXLV22: R179.1, U23.20
RXLV23: R187.1, U24.20
RXLV24: R195.1, U25.20
RXLV25: R203.1, U26.20
RXLV26: R211.1, U27.20
RXLV27: R219.1, U28.20
RXLV28: R227.1, U29.20
RXLV29: R235.1, U30.20
RXLV30: R243.1, U31.20
RXLV31: R251.1, U32.20
RXLV32: R259.1, U33.20
RXLV33: R267.1, U34.20
RXLV34: R275.1, U35.20
RXLV35: R283.1, U36.20
RXLV36: R291.1, U37.20
RXLV37: R299.1, U38.20
RXLV38: R307.1, U39.20
RXLV39: R315.1, U40.20
SCL: J2.4, J3.4, J4.4, R7.1, U1.14
SCL1: J6.4, J8.4, J9.4, R13.1, U2.14
SCL2: J13.4, J14.4, J15.4, R21.1, U3.14
SCL3: J19.4, J20.4, J21.4, R29.1, U4.14
SCL4: J25.4, J26.4, J27.4, R37.1, U5.14
SCL5: J31.4, J32.4, J33.4, R45.1, U6.14
SCL6: J37.4, J38.4, J39.4, R53.1, U7.14
SCL7: J43.4, J44.4, J45.4, R61.1, U8.14
SCL8: J49.4, J50.4, J51.4, R69.1, U9.14
SCL9: J55.4, J56.4, J57.4, R77.1, U10.14
SCL10: J61.4, J62.4, J63.4, R85.1, U11.14
SCL11: J67.4, J68.4, J69.4, R93.1, U12.14
SCL12: J73.4, J74.4, J75.4, R101.1, U13.14
SCL13: J79.4, J80.4, J81.4, R109.1, U14.14
SCL14: J85.4, J86.4, J87.4, R117.1, U15.14
SCL15: J91.4, J92.4, J93.4, R125.1, U16.14
SCL16: J97.4, J98.4, J99.4, R133.1, U17.14
SCL17: J103.4, J104.4, J105.4, R141.1, U18.14
SCL18: J109.4, J110.4, J111.4, R149.1, U19.14
SCL19: J115.4, J116.4, J117.4, R157.1, U20.14
SCL20: J121.4, J122.4, J123.4, R165.1, U21.14
SCL21: J127.4, J128.4, J129.4, R173.1, U22.14
SCL22: J133.4, J134.4, J135.4, R181.1, U23.14
SCL23: J139.4, J140.4, J141.4, R189.1, U24.14
SCL24: J145.4, J146.4, J147.4, R197.1, U25.14
SCL25: J151.4, J152.4, J153.4, R205.1, U26.14
SCL26: J157.4, J158.4, J159.4, R213.1, U27.14
SCL27: J163.4, J164.4, J165.4, R221.1, U28.14
SCL28: J169.4, J170.4, J171.4, R229.1, U29.14
SCL29: J175.4, J176.4, J177.4, R237.1, U30.14
SCL30: J181.4, J182.4, J183.4, R245.1, U31.14
SCL31: J187.4, J188.4, J189.4, R253.1, U32.14
SCL32: J193.4, J194.4, J195.4, R261.1, U33.14
SCL33: J199.4, J200.4, J201.4, R269.1, U34.14
SCL34: J205.4, J206.4, J207.4, R277.1, U35.14
SCL35: J211.4, J212.4, J213.4, R285.1, U36.14
SCL36: J217.4, J218.4, J219.4, R293.1, U37.14
SCL37: J223.4, J224.4, J225.4, R301.1, U38.14
SCL38: J229.4, J230.4, J231.4, R309.1, U39.14
SCL39: J235.4, J236.4, J237.4, R317.1, U40.14
SDA: J2.3, J3.3, J4.3, R8.1, U1.13
SDA1: J6.3, J8.3, J9.3, R14.1, U2.13
SDA2: J13.3, J14.3, J15.3, R22.1, U3.13
SDA3: J19.3, J20.3, J21.3, R30.1, U4.13
SDA4: J25.3, J26.3, J27.3, R38.1, U5.13
SDA5: J31.3, J32.3, J33.3, R46.1, U6.13
SDA6: J37.3, J38.3, J39.3, R54.1, U7.13
SDA7: J43.3, J44.3, J45.3, R62.1, U8.13
SDA8: J49.3, J50.3, J51.3, R70.1, U9.13
SDA9: J55.3, J56.3, J57.3, R78.1, U10.13
SDA10: J61.3, J62.3, J63.3, R86.1, U11.13
SDA11: J67.3, J68.3, J69.3, R94.1, U12.13
SDA12: J73.3, J74.3, J75.3, R102.1, U13.13
SDA13: J79.3, J80.3, J81.3, R110.1, U14.13
SDA14: J85.3, J86.3, J87.3, R118.1, U15.13
SDA15: J91.3, J92.3, J93.3, R126.1, U16.13
SDA16: J97.3, J98.3, J99.3, R134.1, U17.13
SDA17: J103.3, J104.3, J105.3, R142.1, U18.13
SDA18: J109.3, J110.3, J111.3, R150.1, U19.13
SDA19: J115.3, J116.3, J117.3, R158.1, U20.13
SDA20: J121.3, J122.3, J123.3, R166.1, U21.13
SDA21: J127.3, J128.3, J129.3, R174.1, U22.13
SDA22: J133.3, J134.3, J135.3, R182.1, U23.13
SDA23: J139.3, J140.3, J141.3, R190.1, U24.13
SDA24: J145.3, J146.3, J147.3, R198.1, U25.13
SDA25: J151.3, J152.3, J153.3, R206.1, U26.13
SDA26: J157.3, J158.3, J159.3, R214.1, U27.13
SDA27: J163.3, J164.3, J165.3, R222.1, U28.13
SDA28: J169.3, J170.3, J171.3, R230.1, U29.13
SDA29: J175.3, J176.3, J177.3, R238.1, U30.13
SDA30: J181.3, J182.3, J183.3, R246.1, U31.13
SDA31: J187.3, J188.3, J189.3, R254.1, U32.13
SDA32: J193.3, J194.3, J195.3, R262.1, U33.13
SDA33: J199.3, J200.3, J201.3, R270.1, U34.13
SDA34: J205.3, J206.3, J207.3, R278.1, U35.13
SDA35: J211.3, J212.3, J213.3, R286.1, U36.13
SDA36: J217.3, J218.3, J219.3, R294.1, U37.13
SDA37: J223.3, J224.3, J225.3, R302.1, U38.13
SDA38: J229.3, J230.3, J231.3, R310.1, U39.13
SDA39: J235.3, J236.3, J237.3, R318.1, U40.13
TX: J7.5, R6.2
TX1: J11.5, R12.2
TX2: J17.5, R20.2
TX3: J23.5, R28.2
TX4: J29.5, R36.2
TX5: J35.5, R44.2
TX6: J41.5, R52.2
TX7: J47.5, R60.2
TX8: J53.5, R68.2
TX9: J59.5, R76.2
TX10: J65.5, R84.2
TX11: J71.5, R92.2
TX12: J77.5, R100.2
TX13: J83.5, R108.2
TX14: J89.5, R116.2
TX15: J95.5, R124.2
TX16: J101.5, R132.2
TX17: J107.5, R140.2
TX18: J113.5, R148.2
TX19: J119.5, R156.2
TX20: J125.5, R164.2
TX21: J131.5, R172.2
TX22: J137.5, R180.2
TX23: J143.5, R188.2
TX24: J149.5, R196.2
TX25: J155.5, R204.2
TX26: J161.5, R212.2
TX27: J167.5, R220.2
TX28: J173.5, R228.2
TX29: J179.5, R236.2
TX30: J185.5, R244.2
TX31: J191.5, R252.2
TX32: J197.5, R260.2
TX33: J203.5, R268.2
TX34: J209.5, R276.2
TX35: J215.5, R284.2
TX36: J221.5, R292.2
TX37: J227.5, R300.2
TX38: J233.5, R308.2
TX39: J239.5, R316.2
TXLV: R6.1, U1.19
TXLV1: R12.1, U2.19
TXLV2: R20.1, U3.19
TXLV3: R28.1, U4.19
TXLV4: R36.1, U5.19
TXLV5: R44.1, U6.19
TXLV6: R52.1, U7.19
TXLV7: R60.1, U8.19
TXLV8: R68.1, U9.19
TXLV9: R76.1, U10.19
TXLV10: R84.1, U11.19
TXLV11: R92.1, U12.19
TXLV12: R100.1, U13.19
TXLV13: R108.1, U14.19
TXLV14: R116.1, U15.19
TXLV15: R124.1, U16.19
TXLV16: R132.1, U17.19
TXLV17: R140.1, U18.19
TXLV18: R148.1, U19.19
TXLV19: R156.1, U20.19
TXLV20: R164.1, U21.19
TXLV21: R172.1, U22.19
TXLV22: R180.1, U23.19
TXLV23: R188.1, U24.19
TXLV24: R196.1, U25.19
TXLV25: R204.1, U26.19
TXLV26: R212.1, U27.19
TXLV27: R220.1, U28.19
TXLV28: R228.1, U29.19
TXLV29: R236.1, U30.19
TXLV30: R244.1, U31.19
TXLV31: R252.1, U32.19
TXLV32: R260.1, U33.19
TXLV33: R268.1, U34.19
TXLV34: R276.1, U35.19
TXLV35: R284.1, U36.19
TXLV36: R292.1, U37.19
TXLV37: R300.1, U38.19
TXLV38: R308.1, U39.19
TXLV39: R316.1, U40.19
VCC_FILTERED: C1.1, C2.1, FB1.2, U1.7
VCC_FILTERED1: C5.1, C6.1, FB2.2, U2.7
VCC_FILTERED2: C9.1, C10.1, FB3.2, U3.7
VCC_FILTERED3: C13.1, C14.1, FB4.2, U4.7
VCC_FILTERED4: C17.1, C18.1, FB5.2, U5.7
VCC_FILTERED5: C21.1, C22.1, FB6.2, U6.7
VCC_FILTERED6: C25.1, C26.1, FB7.2, U7.7
VCC_FILTERED7: C29.1, C30.1, FB8.2, U8.7
VCC_FILTERED8: C33.1, C34.1, FB9.2, U9.7
VCC_FILTERED9: C37.1, C38.1, FB10.2, U10.7
VCC_FILTERED10: C41.1, C42.1, FB11.2, U11.7
VCC_FILTERED11: C45.1, C46.1, FB12.2, U12.7
VCC_FILTERED12: C49.1, C50.1, FB13.2, U13.7
VCC_FILTERED13: C53.1, C54.1, FB14.2, U14.7
VCC_FILTERED14: C57.1, C58.1, FB15.2, U15.7
VCC_FILTERED15: C61.1, C62.1, FB16.2, U16.7
VCC_FILTERED16: C65.1, C66.1, FB17.2, U17.7
VCC_FILTERED17: C69.1, C70.1, FB18.2, U18.7
VCC_FILTERED18: C73.1, C74.1, FB19.2, U19.7
VCC_FILTERED19: C77.1, C78.1, FB20.2, U20.7
VCC_FILTERED20: C81.1, C82.1, FB21.2, U21.7
VCC_FILTERED21: C85.1, C86.1, FB22.2, U22.7
VCC_FILTERED22: C89.1, C90.1, FB23.2, U23.7
VCC_FILTERED23: C93.1, C94.1, FB24.2, U24.7
VCC_FILTERED24: C97.1, C98.1, FB25.2, U25.7
VCC_FILTERED25: C101.1, C102.1, FB26.2, U26.7
VCC_FILTERED26: C105.1, C106.1, FB27.2, U27.7
VCC_FILTERED27: C109.1, C110.1, FB28.2, U28.7
VCC_FILTERED28: C113.1, C114.1, FB29.2, U29.7
VCC_FILTERED29: C117.1, C118.1, FB30.2, U30.7
VCC_FILTERED30: C121.1, C122.1, FB31.2, U31.7
VCC_FILTERED31: C125.1, C126.1, FB32.2, U32.7
VCC_FILTERED32: C129.1, C130.1, FB33.2, U33.7
VCC_FILTERED33: C133.1, C134.1, FB34.2, U34.7
VCC_FILTERED34: C137.1, C138.1, FB35.2, U35.7
VCC_FILTERED35: C141.1, C142.1, FB36.2, U36.7
VCC_FILTERED36: C145.1, C146.1, FB37.2, U37.7
VCC_FILTERED37: C149.1, C150.1, FB38.2, U38.7
VCC_FILTERED38: C153.1, C154.1, FB39.2, U39.7
VCC_FILTERED39: C157.1, C158.1, FB40.2, U40.7
WAKE: J7.1, R1.2, U1.12
WAKE1: J11.1, R4.2, U2.12
WAKE2: J17.1, R17.2, U3.12
WAKE3: J23.1, R25.2, U4.12
WAKE4: J29.1, R33.2, U5.12
WAKE5: J35.1, R41.2, U6.12
WAKE6: J41.1, R49.2, U7.12
WAKE7: J47.1, R57.2, U8.12
WAKE8: J53.1, R65.2, U9.12
WAKE9: J59.1, R73.2, U10.12
WAKE10: J65.1, R81.2, U11.12
WAKE11: J71.1, R89.2, U12.12
WAKE12: J77.1, R97.2, U13.12
WAKE13: J83.1, R105.2, U14.12
WAKE14: J89.1, R113.2, U15.12
WAKE15: J95.1, R121.2, U16.12
WAKE16: J101.1, R129.2, U17.12
WAKE17: J107.1, R137.2, U18.12
WAKE18: J113.1, R145.2, U19.12
WAKE19: J119.1, R153.2, U20.12
WAKE20: J125.1, R161.2, U21.12
WAKE21: J131.1, R169.2, U22.12
WAKE22: J137.1, R177.2, U23.12
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
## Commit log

2017-06-16 added eagle files
2017-06-19 Added readme, .gitignore, etc...
2017-06-20 Updated file structure to match SFE repo
2017-06-20 Added SparkX models to Sparkfun Library
2017-07-07 fixed DRC errors, updated board to meet checklist
2017-07-12 Added jumper functions to schematic and board
2017-07-12 Post design review changes fixed
2017-07-13 changed corner of GPS package
2017-07-18 V02 changed some net issues, board thicknessinstruction
2017-07-25 changed version
2017-08-15 Changed version number, moved int pin to be compatible with arduino, added jumper label for pps led
2017-08-15 fixed dimensions
2017-08-15 updated version number
2017-08-23 Moved engineering checklist
2017-08-30 panel
2017-10-18 preparing library for release
2017-10-18 Updating library
2017-10-18 Squashed 'Libraries/Arduino/' content from commit e522651
    git-subtree-dir: Libraries/Arduino
    git-subtree-split: e52265138e1c272fa5e4aa6fda785ac866e6cf0d
2017-10-18 Continuing to clean repo
2017-10-18 Squashed 'Libraries/TinyGPS/' content from commit db4ef9c
    git-subtree-dir: Libraries/TinyGPS
    git-subtree-split: db4ef9c97af767e7345f5ccb277ac3bd1a2eb81f
2017-10-18 Initial release
